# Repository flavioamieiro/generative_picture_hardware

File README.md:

This repository includes the design files for the hardware of the
Generative Picture project (this name will probably change). The
schematics and PCB layout are done in Kicad and all extra libraries
necessary to edit the project should be included here. If you find any
issues, please let me know.

This source describes Open Hardware and is licensed under the
CERN-OHL-S v2.  You may redistribute and modify this source and make
products using it under the terms of the CERN-OHL-S v2
(https://ohwr.org/cern_ohl_s_v2.txt).

This source is distributed WITHOUT ANY EXPRESS OR IMPLIED WARRANTY,
INCLUDING OF MERCHANTABILITY, SATISFACTORY QUALITY AND FITNESS FOR A
PARTICULAR PURPOSE. Please see the CERN-OHL-S v2 for applicable
conditions.

Source location:
https://github.com/flavioamieiro/generative_picture_hardware

As per CERN-OHL-S v2 section 4, should You produce hardware based on
this source, You must where practicable maintain the Source Location
visible on the external case of the Gizmo or other products you make
using this source.

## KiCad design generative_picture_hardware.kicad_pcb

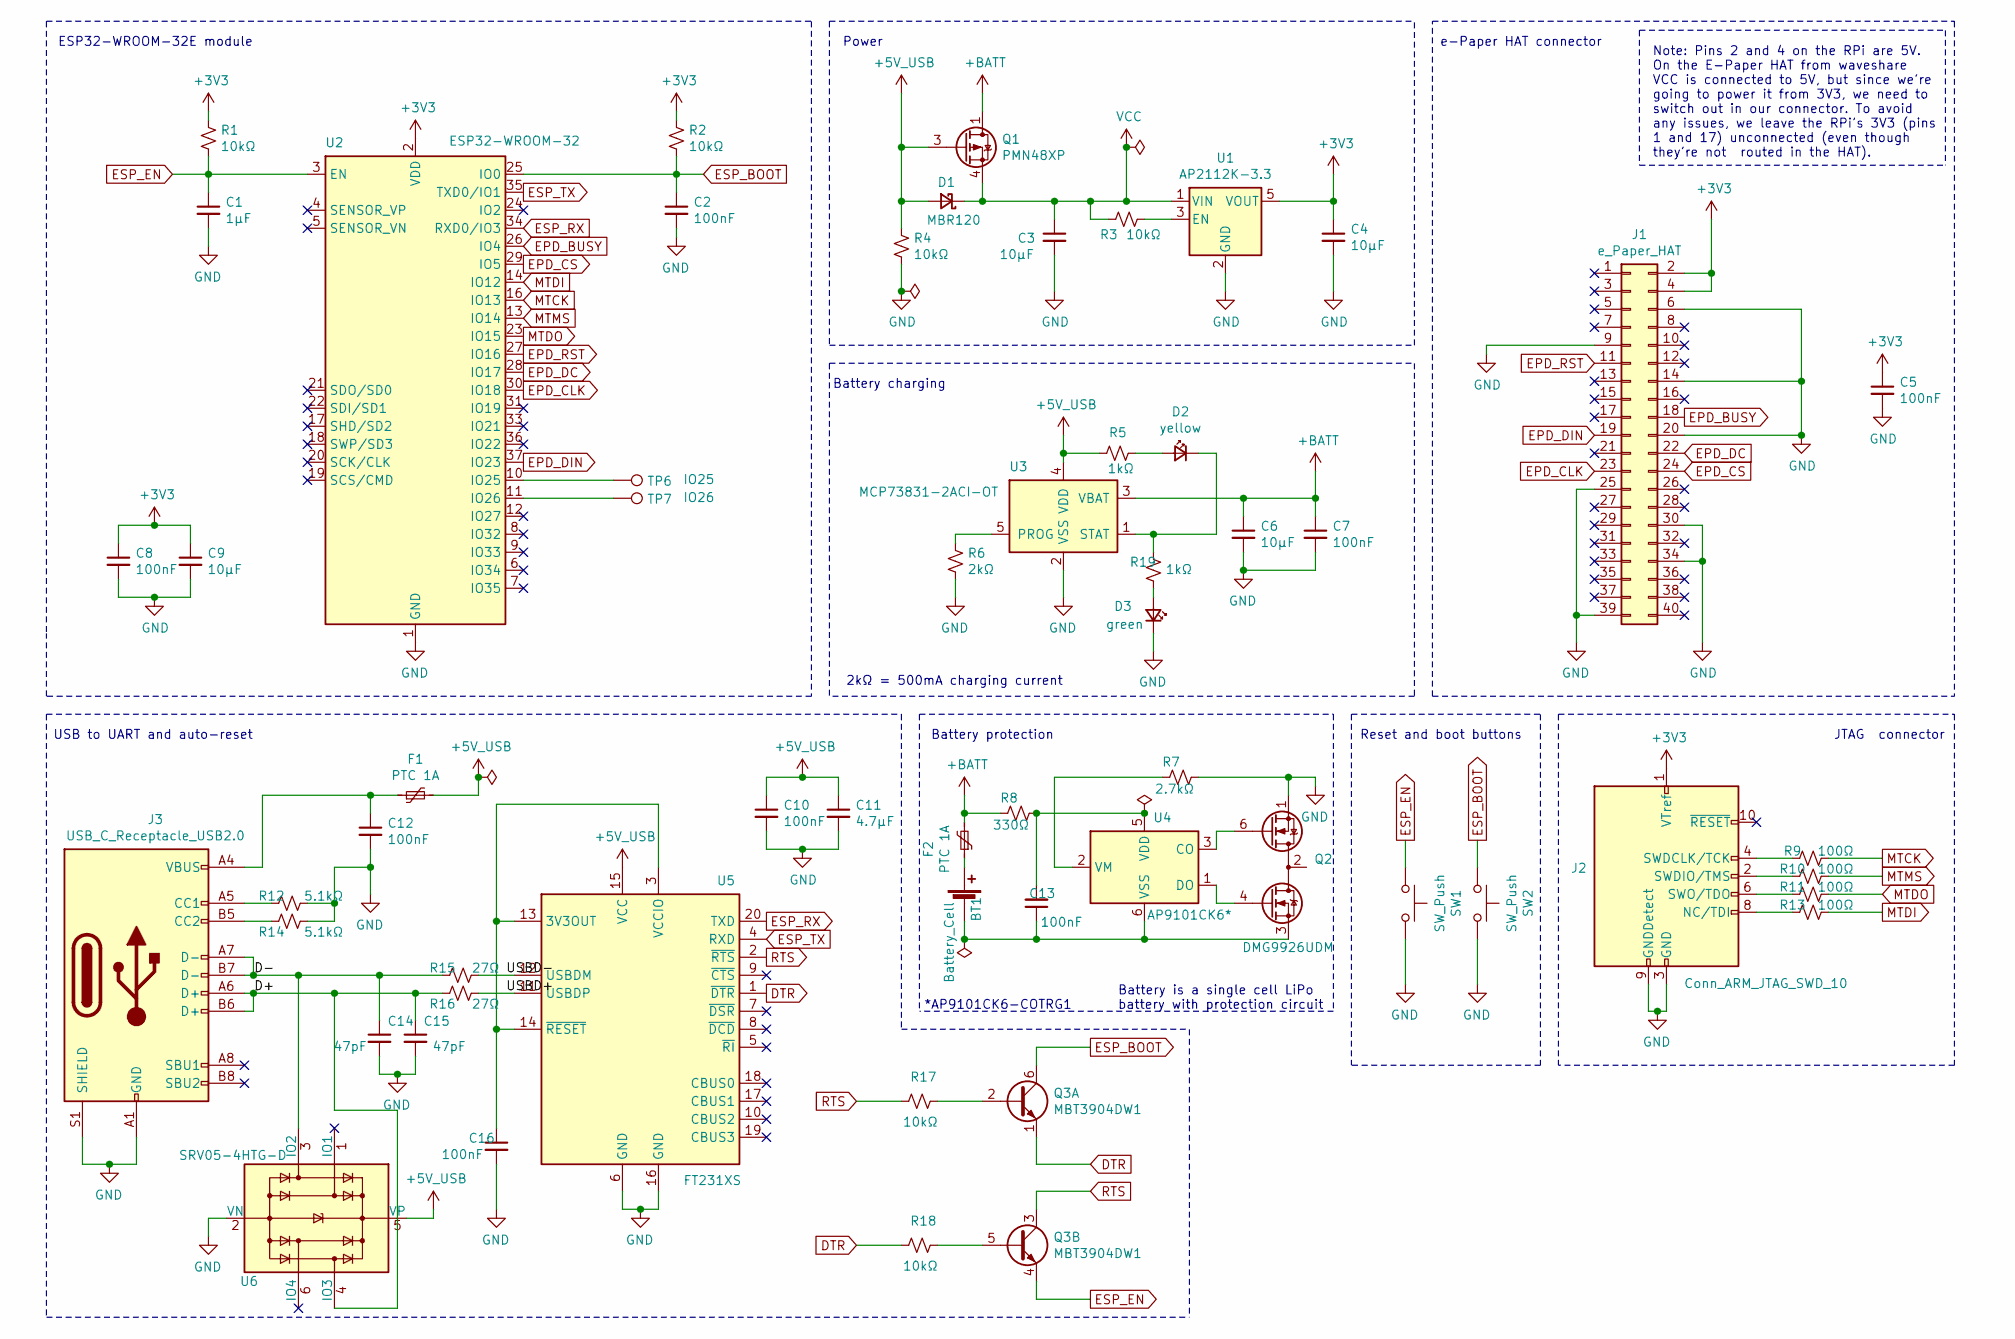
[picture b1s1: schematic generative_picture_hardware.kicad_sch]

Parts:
BT1: Battery_Cell; JST_PH_S2B-PH-SM4-TB_1x02-1MP_P2.00mm_Horizontal
C1: 1µF; C_0805_2012Metric_Pad1.18x1.45mm_HandSolder
C2, C5, C7, C8, C10, C12, C13, C16: 100nF; C_0805_2012Metric_Pad1.18x1.45mm_HandSolder
C3, C4, C6, C9: 10µF; C_0805_2012Metric_Pad1.18x1.45mm_HandSolder
C11: 4.7µF; C_0805_2012Metric_Pad1.18x1.45mm_HandSolder
C14, C15: 47pF; C_0805_2012Metric_Pad1.18x1.45mm_HandSolder
D1: MBR120; D_SOD-123
D2: yellow; LED_0805_2012Metric_Pad1.15x1.40mm_HandSolder
D3: green; LED_0805_2012Metric_Pad1.15x1.40mm_HandSolder
F1, F2: PTC 1A; Belfuse_0ZCJ
J1: e_Paper_HAT; e-Paper_display_HAT
J2: Conn_ARM_JTAG_SWD_10; PinHeader_2x05_P2.54mm_Vertical
J3: USB_C_Receptacle_USB2.0; USB_C_Receptacle_JAE_DX07S016JA1
Q1: PMN48XP; TSOP-6_1.65x3.05mm_P0.95mm
Q2: DMG9926UDM; SOT-23-6
Q3: MBT3904DW1; SOT-363_SC-70-6
R1, R2, R3, R4, R17, R18: 10kΩ; R_0805_2012Metric_Pad1.20x1.40mm_HandSolder
R5, R19: 1kΩ; R_0805_2012Metric_Pad1.20x1.40mm_HandSolder
R6: 2kΩ; R_0805_2012Metric_Pad1.20x1.40mm_HandSolder
R7: 2.7kΩ; R_0805_2012Metric_Pad1.20x1.40mm_HandSolder
R8: 330Ω; R_0805_2012Metric_Pad1.20x1.40mm_HandSolder
R9, R10, R11, R13: 100Ω; R_0805_2012Metric_Pad1.20x1.40mm_HandSolder
R12, R14: 5.1kΩ; R_0805_2012Metric_Pad1.20x1.40mm_HandSolder
R15, R16: 27Ω; R_0805_2012Metric_Pad1.20x1.40mm_HandSolder
SW1, SW2: SW_Push; SWITCH_TACTILE_CK_PTS636_SK43_SMTR_LFS
TP6: IO25; TestPoint_Pad_D2.0mm
TP7: IO26; TestPoint_Pad_D2.0mm
U1: AP2112K-3.3; SOT-23-5
U2: ESP32-WROOM-32
U3: MCP73831-2ACI-OT; SOT-23-5
U4: AP9101CK6*; SOT-23-6
U5: FT231XS; SSOP-20_3.9x8.7mm_P0.635mm
U6: SRV05-4HTG-D; SOT-23-6

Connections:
+3V3: C4.1, C5.1, C8.1, C9.1, J1.2, J1.4, J2.1 (VTref), R1.1, R2.1, U1.5 (VOUT), U2.2 (VDD)
+5V: C10.1, C11.1, D1.2 (A), F1.2, Q1.3 (G), R4.1, R5.1, U3.4 (VDD), U5.15 (VCC), U6.5 (VP)
+BATT: C6.1, C7.1, F2.2, Q1.1 (D), Q1.2 (D), Q1.5 (D), Q1.6 (D), R8.2, U3.3 (VBAT)
/D+: C15.1, J3.A6 (D+), J3.B6 (D+), R16.1, U6.4 (IO3)
/D-: C14.1, J3.A7 (D-), J3.B7 (D-), R15.1, U6.3 (IO2)
/USBD+: R16.2, U5.11 (USBDP)
/USBD-: R15.2, U5.12 (USBDM)
DTR: Q3.1 (E1), R18.2, U5.1 (~DTR)
EPD_BUSY: J1.18, U2.26 (IO4)
EPD_CLK: J1.23, U2.30 (IO18)
EPD_CS: J1.24, U2.29 (IO5)
EPD_DC: J1.22, U2.28 (IO17)
EPD_DIN: J1.19, U2.37 (IO23)
EPD_RST: J1.11, U2.27 (IO16)
ESP_BOOT: C2.1, Q3.6 (C1), R2.2, SW2.1, U2.25 (IO0)
ESP_EN: C1.1, Q3.4 (E2), R1.2, SW1.1, U2.3 (EN)
ESP_RX: U2.34 (RXD0/IO3), U5.20 (TXD)
ESP_TX: U2.35 (TXD0/IO1), U5.4 (RXD)
GND: C1.2, C2.2, C3.2, C4.2, C5.2, C6.2, C7.2, C8.2, C9.2, C10.2, C11.2, C12.2, C14.2, C15.2, C16.2, D3.1 (K), J1.6, J1.9, J1.14, J1.20, J1.25, J1.30, J1.34, J1.39, J2.3 (GND), J2.5 (GND), J2.9 (GNDDetect), J3.A1 (GND), J3.A12 (GND), J3.B1 (GND), J3.B12 (GND), J3.S1 (SHIELD), Q2.1 (D1), R4.2, R6.2, R7.1, R12.2, R14.2, SW1.2, SW2.2, U1.2 (GND), U2.1 (GND), U2.15 (GND), U2.38 (GND), U2.39 (GND), U3.2 (VSS), U5.6 (GND), U5.16 (GND), U6.2 (VN)
MTCK: R9.2, U2.16 (IO13)
MTDI: R13.2, U2.14 (IO12)
MTDO: R11.2, U2.23 (IO15)
MTMS: R10.2, U2.13 (IO14)
unnamed: BT1.1 (+), F2.1
unnamed: BT1.2 (-), C13.1, Q2.3 (S2), U4.6 (VSS)
unnamed: C12.1, F1.1, J3.A4 (VBUS), J3.A9 (VBUS), J3.B4 (VBUS), J3.B9 (VBUS)
unnamed: C13.2, R8.1, U4.5 (VDD)
unnamed: C16.1, U5.3 (VCCIO), U5.13 (3V3OUT), U5.14 (~RESET)
unnamed: D2.1 (K), R19.1, U3.1 (STAT)
unnamed: D2.2 (A), R5.2
unnamed: D3.2 (A), R19.2
unnamed: J2.2 (SWDIO/TMS), R10.1
unnamed: J2.4 (SWDCLK/TCK), R9.1
unnamed: J2.6 (SWO/TDO), R11.1
unnamed: J2.8 (NC/TDI), R13.1
unnamed: J3.A5 (CC1), R12.1
unnamed: J3.B5 (CC2), R14.1
unnamed: Q2.2 (S1/D2), Q2.5 (S1/D2)
unnamed: Q2.4 (G2), U4.1 (DO)
unnamed: Q2.6 (G1), U4.3 (CO)
unnamed: Q3.2 (B1), R17.1
unnamed: Q3.5 (B2), R18.1
unnamed: R3.2, U1.3 (EN)
unnamed: R6.1, U3.5 (PROG)
unnamed: R7.2, U4.2 (VM)
unnamed: TP6.1, U2.10 (IO25)
unnamed: TP7.1, U2.11 (IO26)
RTS: Q3.3 (C2), R17.2, U5.2 (~RTS)
VCC: C3.1, D1.1 (K), Q1.4 (S), R3.1, U1.1 (VIN)

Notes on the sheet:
ESP32-WROOM-32E module
USB to UART and auto-reset
Power
Battery charging
Battery protection
2kΩ = 500mA charging current
*AP9101CK6-COTRG1
Battery is a single cell LiPo battery with protection circuit
Reset and boot buttons
e-Paper HAT connector
Note: Pins 2 and 4 on the RPi are 5V. On the E-Paper HAT from waveshare VCC is connected to 5V, but since we're going to power it from 3V3, we need to switch out in our connector. To avoid any issues, we leave the RPi's 3V3 (pins 1 and 17) unconnected (even though they're not routed in the HAT).
JTAG connector

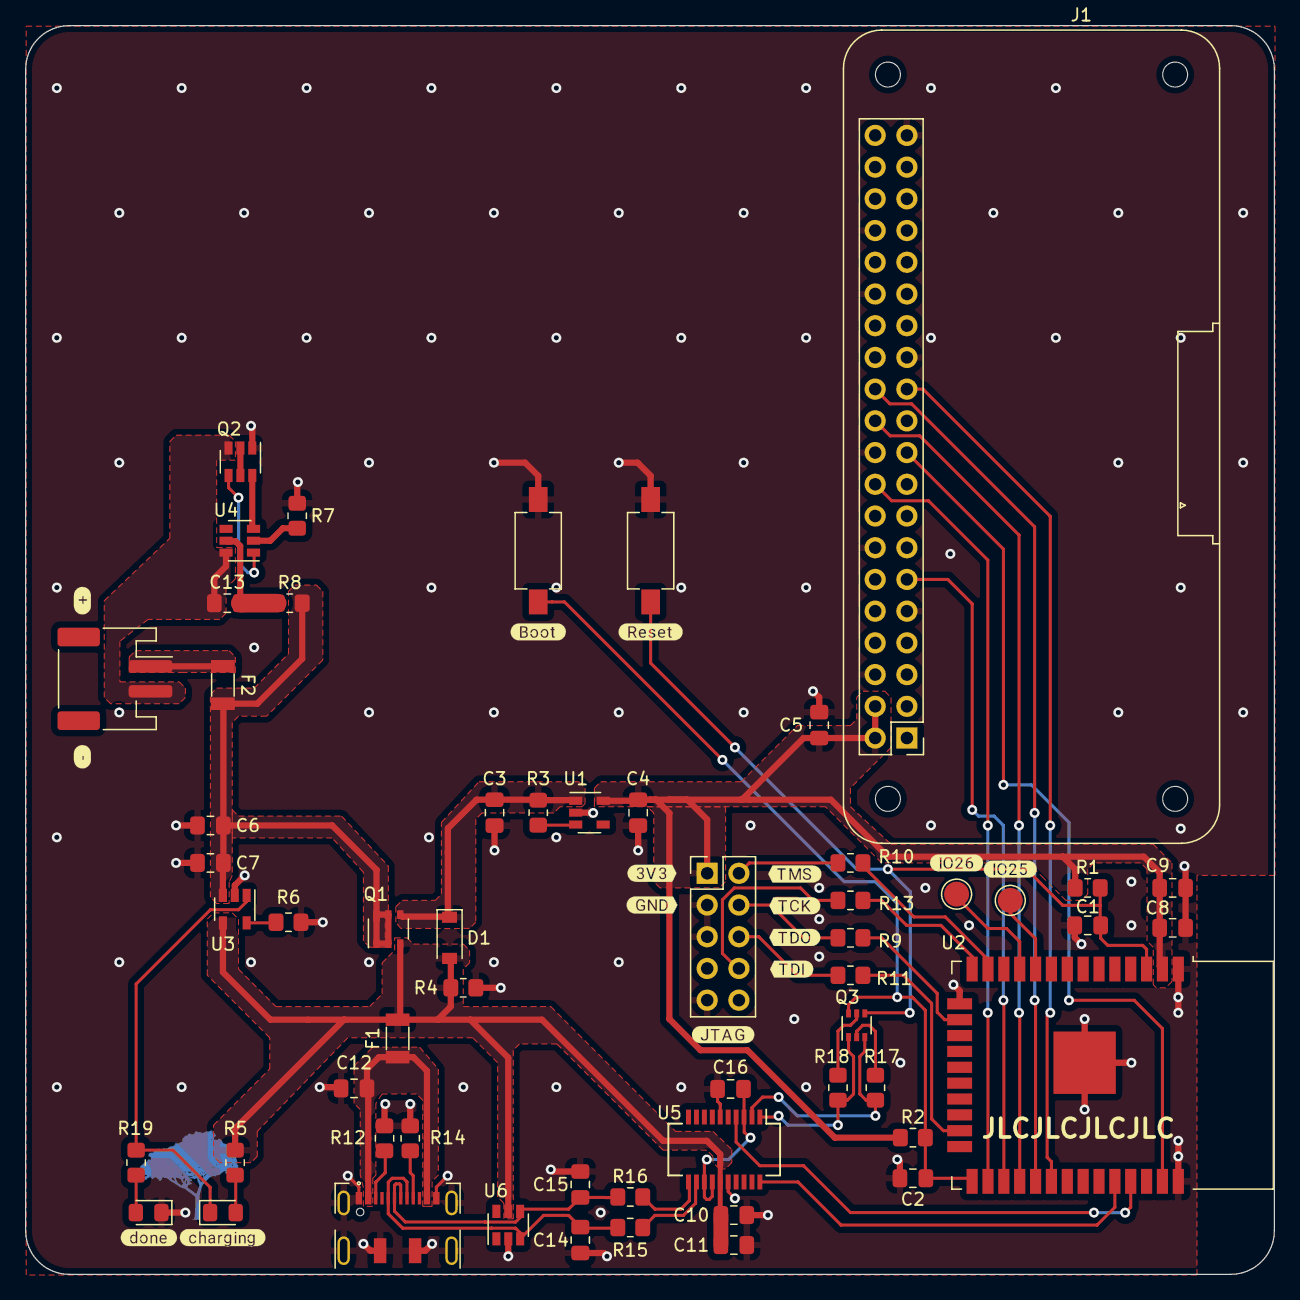
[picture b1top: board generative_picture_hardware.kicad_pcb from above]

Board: 2 copper layers, 100.0 x 100.0 mm, 59 parts (0 on the bottom side), 49 nets.

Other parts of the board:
Ref**: Val**; url_bsilks
Ref**#2: Val**; ipe_logo

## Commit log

2021-01-23 Initial commit (empty kicad project)
2021-01-24 Start the schematics by connecting the HAT pins to the ESP32
    The VCC on the e-Paper HAT is connected to 5V[1], but we will power it from
    the 3V3 rails as I did in all my tests*. Because of that, we can't
    replicate the pinout of the raspberry Pi header exactly. Instead, we
    connect 3V3 to where 5V is on the Pi and leave the pins where the Pi has
    3V3 unconnected (even though they're not routed in the HAT).
    * The level shifter in the HAT (a TXS0108E[2]) takes from 1.65 to 5.5V on the
2021-01-24 Adds JTAG connector
    I'm using 100Ω series resistors in the JTAG lines as per the reference
    design in the ESP32-WROOM-32 datasheet[1] (section 7).
    [1]: https://www.espressif.com/sites/default/files/documentation/esp32-wroom-32_datasheet_en.pdf
2021-01-25 Adds minimal circuit around the ESP32 module
2021-02-01 Adds USB to UART converter and auto-reset circuit
    I'm using the FTDI FT231XS USB to UART converter IC. There's also a
    TVS diode array for ESD protection, which might be overkill but I
    decided to add it anyways.
2021-02-01 Adds boot button and fixes global label directions
2021-02-01 Adds LiPo charging circuit
    Uses the MCP73831 to charge a single cell LiPo battery that should
    have undervoltage protection builtin[1]
    [1]: Such as https://www.adafruit.com/product/328
2021-02-01 Adds LDO regulator circuit
    This circuit uses a p-channel MOSFET to switch the power supply to the
    regulator from battery to USB when the cable is plugged in[1].
    [1]: https://www.youtube.com/watch?v=GRd9uTwg7r4
2021-02-01 Adds annotations and fixes small issues after ERC
2021-02-03 Reorganizes auto-reset circuit
    This makes it more clear and better aligned.
2021-02-03 Adds battery protection circuit with AP9101
2021-02-03 Adds test points to some of the remaining GPIO pins of the ESP32
2021-02-05 Adds a second LED to indicate the charging is complete and assigns some footprints
    As per table 5-1 in the MCP73831 datasheet[1], the STAT pin is low while
    charging, high when charge is complete and high impedance when the IC is
    shutdown or there is no battery present:
    +----------+--------+
    | Charging |STAT pin|
    +----------+--------+
2021-02-05 Adds footprint for Bourns MF-NSHT PTC resettable Fuse
2021-02-05 Adds JAE_DX07S016JA1 USB-C receptacle footprint from @adamws
    Based on the opened Pull Request[1][2] by Adam Wysocki. Thank you!
    [1]: https://github.com/KiCad/kicad-footprints/pull/2098
    [2]: https://gitlab.com/kicad/libraries/kicad-footprints/-/merge_requests/2098/diffs
2021-02-07 Adds footprint for CK PTS636 SK43 SMTR LFS pushbutton
2021-02-07 Associates footprints to components in the schematics
2021-02-07 Adds Footprint for the e-Paper display HAT
2021-02-07 Assigns custom footprint for e-Paper display HAT
2021-02-08 Fixes e-paper HAT connector footprint
2021-02-08 Renames e-Paper DIN pin
2021-02-08 Adds labels to USB data lines to allow for routing as differential pairs
2021-02-08 Changes pins on the TVS diodes to make it easier to route
2021-02-08 Removes some unused test points
    They have no immediate use and wouldn't be trivial to route.
2021-02-08 Fixes small issues with the e-Paper hat connector footprint
    There courtyard was self-intersecting, so I removed the FFC connector's
    courtyard (since it's actually raised above the PCB on the connected
    board). The silkscreen and fab layers for the pin header were also
    misaligned.
2021-02-08 Fixes silkscreen overlaping pads in the tactile switch footprint
2021-02-10 Adds first (really) rough layout for the PCB
    There is some really bad routing and the GND is not completely routed.
2021-02-10 Reroutes TVS diodes in USB line
2021-02-10 Routes missing boot and reset lines from reset circuit
2021-02-10 Routes (temporarily) some of the missing 3v3 lines
2021-02-15 Fixes the size for the HAT mounting holes
    The mounting holes on the HAT are M2.5 but the standoffs are M2.
2021-02-15 Fixes clearance between Vbus track and usb connector mounting hole
    This will probably need to be reworked once I increase the thickness for
    the power lines.
2021-02-15 Routes all ground without relying on the top copper fill
2021-02-15 Deletes all tracks and (very) roughly repositions groups of components
2021-02-15 Routes USB to UART
2021-02-15 Reroutes battery charging, protection and regulator
2021-02-15 Removes some more test points for GPIO pins
    I don't really have any use planned for them. Two should be plenty if
    needed at all.
2021-02-15 Reroutes the components that were left (except for GND)
2021-02-15 Routes all GND without relying on front copper fill
2021-02-17 Organizes silkscreen a bit
    This is not final, but it removes the silkscreen related DRC errors.
2021-02-17 Fixes error in the tracks out of the USB plug
2021-02-17 moves JTAG connector so we have more space for the labels
2021-02-17 Removes battery test points and adds labels to JTAG connector
2021-02-17 Removes copper fills from below the antenna keepout area
2021-02-17 Adds some vias to stitch the bottom and top ground planes
2021-02-17 Adds some more labels
2021-02-17 Cleans up the extra vias
2021-02-17 Adds logo
2021-02-19 Brings FTDI chip closer to the usb plug
    This shortens the differential pair track lenghts.
2021-02-19 Adds stitching vias
2021-02-19 Uses copper fills for the battery power traces
2021-02-19 Uses copper fills for 5V rail
2021-02-19 Uses copper fill for VCC path to regulator
2021-02-19 Uses copper fills for 3v3 rail
2021-02-20 Adjust logo position
2021-02-20 Adjusts some of the interactions between pads and copper fills
2021-02-20 Adds JLCPCB order number placeholder adjusts silkscreen some more
2021-02-20 Changes PTC footprint
    It's still 1206 but with slightly wider pads.
2021-02-21 Adds logo back and revision number (0.1)
2021-02-21 Plot Gerbers for rev 0.1
2021-03-14 Switches C8 and C9 placement in the layout
2021-03-14 Adds small README file
2021-03-14 Adds license information
2021-03-14 Adds schematics PDF for easier access
2021-03-14 Adds board render as a STEP file
2021-03-14 Adds image of the board to the README file
2021-03-25 Adds Manufacturer Part Number to some components
    This helps building a more useful BOM. I left out the resistors and
    capacitors as the specific part is not so important.
